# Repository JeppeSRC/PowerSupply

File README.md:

# PowerSupply
Software, schematic and layout for kind of a PSU

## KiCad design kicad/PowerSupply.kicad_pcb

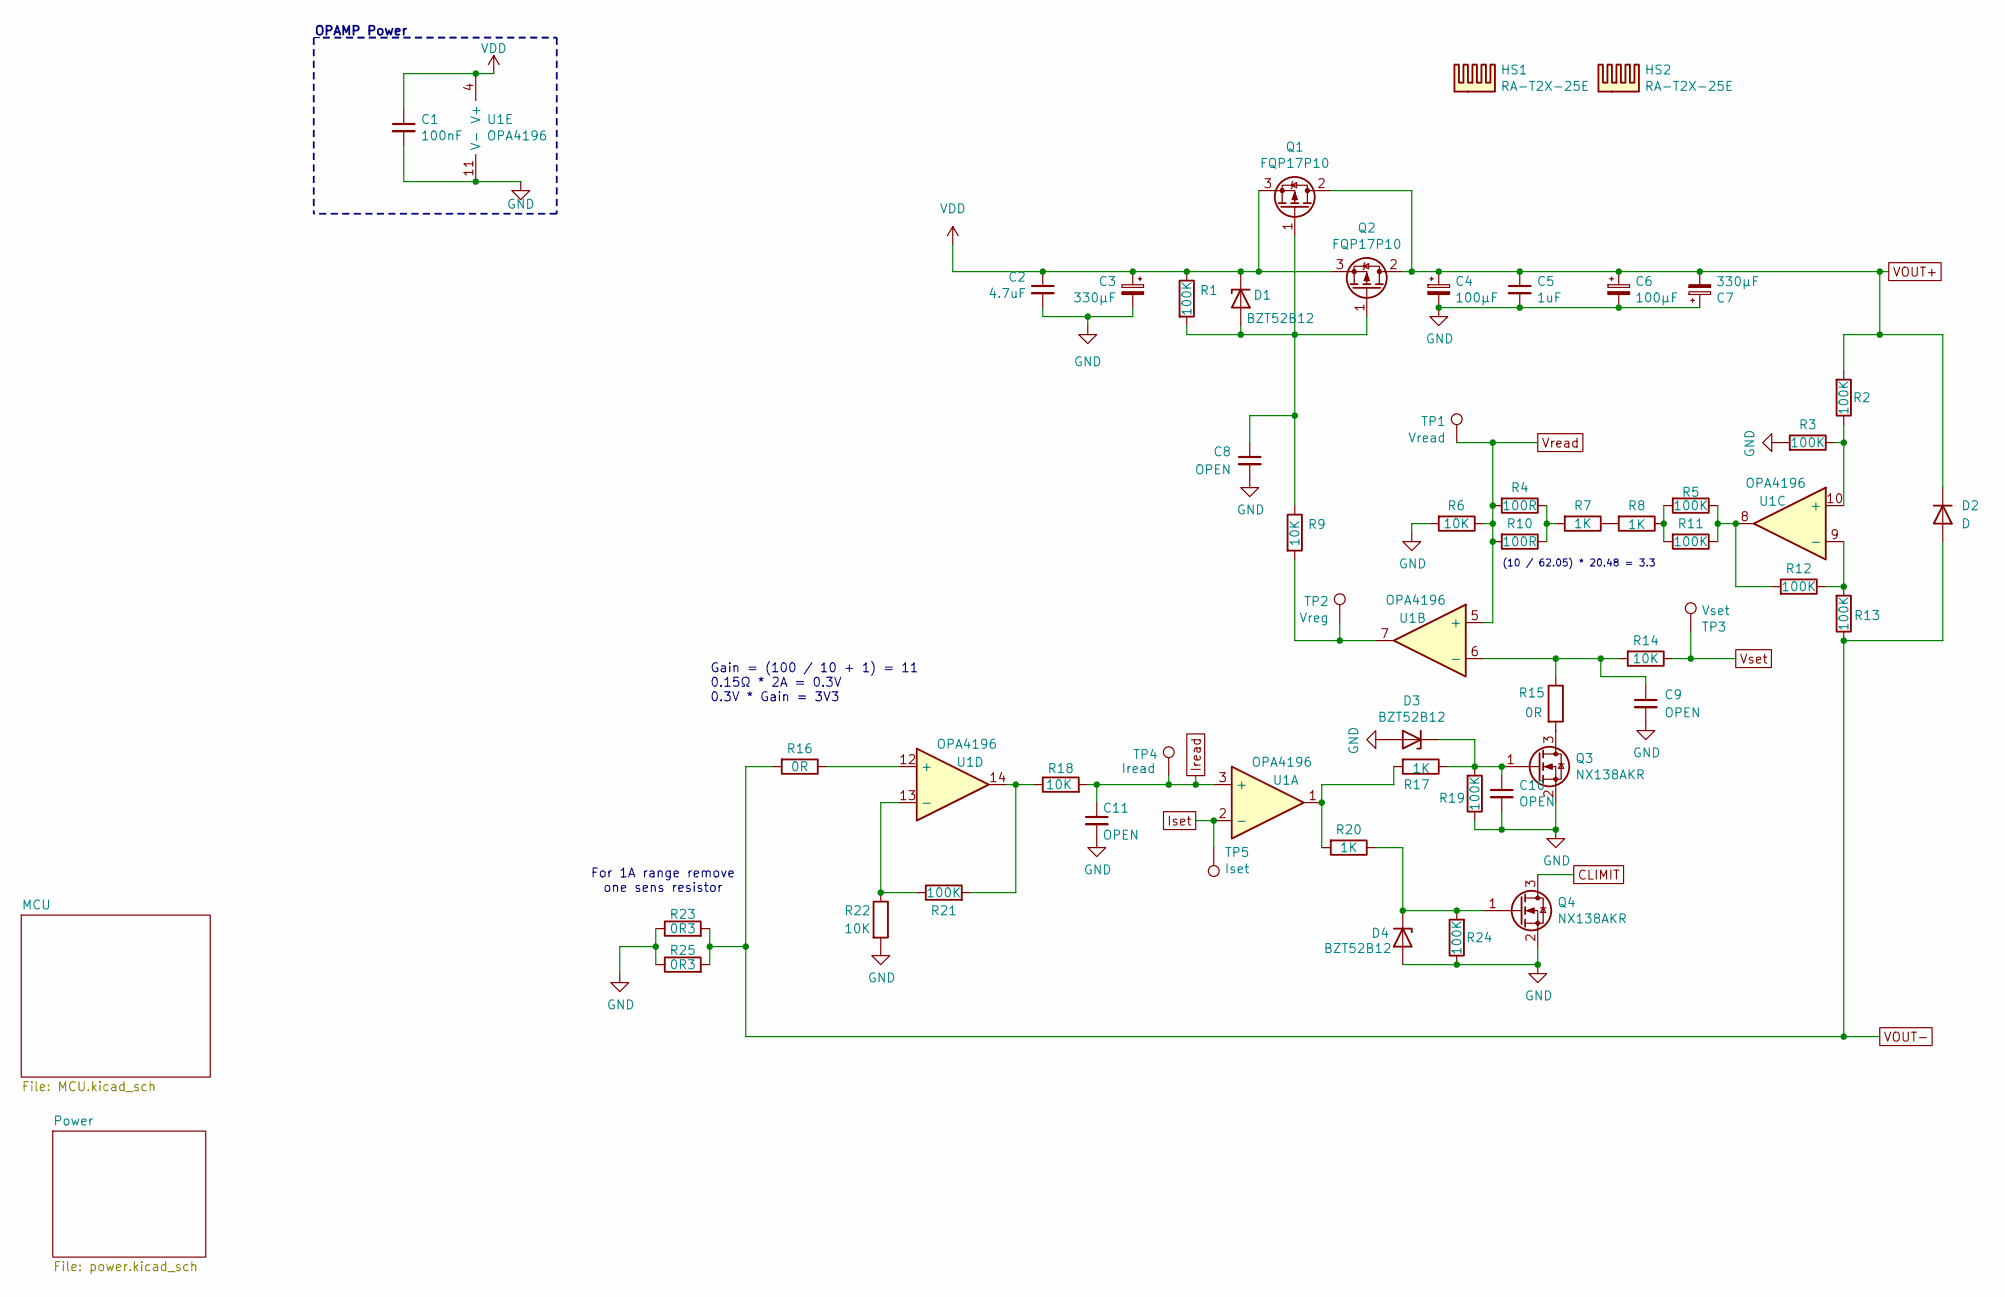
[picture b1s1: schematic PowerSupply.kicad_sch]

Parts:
C1: 100nF; C_0805_2012Metric_Pad1.18x1.45mm_HandSolder; MPN CC0805KRX7R9BB104
C2: 4.7uF; C_0805_2012Metric_Pad1.18x1.45mm_HandSolder; MPN GRM21BR61H475ME51L
C3, C7: 330µF; CP_Radial_D8.0mm_P3.50mm; MPN REA471M1EBK-1012P
C4, C6: 100µF; CP_Radial_D8.0mm_P3.50mm; MPN EKZN500ELL101MHB5D
C5: 1uF; C_0805_2012Metric_Pad1.18x1.45mm_HandSolder; MPN CL21B105KBFNNNF
C8, C9, C10, C11: OPEN; C_0805_2012Metric_Pad1.18x1.45mm_HandSolder
D1, D3, D4: BZT52B12; D_SOD-123; MPN BZT52B12
D2: D; D_SMA_Handsoldering
HS1, HS2: RA-T2X-25E; MPN RA-T2X-25E
Q1, Q2: FQP17P10; TO-220-3_Vertical; MPN FQP17P10
Q3, Q4: NX138AKR; SOT-23-3; MPN NX138AKR
R1, R2, R3, R5, R11, R12, R13, R19, R21, R24: 100K; R_0805_2012Metric_Pad1.20x1.40mm_HandSolder; MPN CRCW080510K0FKEAC
R4, R10: 100R; R_0805_2012Metric_Pad1.20x1.40mm_HandSolder; MPN RC0805FR-13100RL
R6, R9, R14, R18, R22: 10K; R_0805_2012Metric_Pad1.20x1.40mm_HandSolder; MPN RC0805FR-1310KL
R7, R8, R17, R20: 1K; R_0805_2012Metric_Pad1.20x1.40mm_HandSolder; MPN RC0805FR-131KL
R15, R16: 0R; R_0805_2012Metric_Pad1.20x1.40mm_HandSolder; MPN 0805W8J0000T5E
R23, R25: 0R3; R_0805_2012Metric_Pad1.20x1.40mm_HandSolder; MPN CRL1206-FW-R300ELF
TP1: Vread; TestPoint_Pad_D1.5mm
TP2: Vreg; TestPoint_Pad_D1.5mm
TP3: Vset; TestPoint_Pad_D1.5mm
TP4: Iread; TestPoint_Pad_D1.0mm
TP5: Iset; TestPoint_Pad_D1.0mm
U1: OPA4196; SOIC-14_3.9x8.7mm_P1.27mm; MPN OPA4196IDR

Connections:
CLIMIT: Q4.3 (D); also elsewhere on the board
GND: C1.2, C2.2, C3.2, C4.2, C5.2, C6.2, C7.1, C8.2, C9.2, C10.2, C11.2, D3.2 (A), D4.2 (A), Q3.2 (S), Q4.2 (S), R3.2, R6.2, R19.1, R22.2, R23.1, R24.1, R25.1, U1.11 (V-); also elsewhere on the board
Iread: C11.1, R18.2, TP4.1, U1.3 (+); also elsewhere on the board
Iset: TP5.1, U1.2 (-); also elsewhere on the board
unnamed: C8.1, D1.2 (A), Q1.1 (G), Q2.1 (G), R1.2, R9.1
unnamed: C10.1, D3.1 (K), Q3.1 (G), R17.1, R19.2
unnamed: D4.1 (K), Q4.1 (G), R20.1, R24.2
unnamed: Q3.3 (D), R15.2
unnamed: R7.1, R8.2
unnamed: R9.2, TP2.1, U1.7
unnamed: R4.1, R7.2, R10.1
unnamed: R5.1, R11.1, R12.2, U1.8
unnamed: R5.2, R8.1, R11.2
unnamed: R17.2, R20.2, U1.1
unnamed: R18.1, R21.2, U1.14
unnamed: C9.1, R14.2, R15.1, U1.6 (-)
unnamed: R2.1, R3.1, U1.10 (+)
unnamed: R12.1, R13.2, U1.9 (-)
unnamed: R16.1, U1.12 (+)
unnamed: R21.1, R22.1, U1.13 (-)
VDD: C1.1, C2.1, C3.1, D1.1 (K), Q1.3 (S), Q2.3 (S), R1.1, U1.4 (V+); also elsewhere on the board
VOUT+: C4.1, C5.1, C6.1, C7.2, D2.1 (K), Q1.2 (D), Q2.2 (D), R2.2; also elsewhere on the board
VOUT-: D2.2 (A), R13.1, R16.2, R23.2, R25.2; also elsewhere on the board
Vread: R4.2, R6.1, R10.2, TP1.1, U1.5 (+); also elsewhere on the board
Vset: R14.1, TP3.1; also elsewhere on the board

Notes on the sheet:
OPAMP Power
(10 / 62.05) * 20.48 = 3.3
Gain = (100 / 10 + 1) = 11 0.15Ω * 2A = 0.3V 0.3V * Gain = 3V3
For 1A range remove one sens resistor

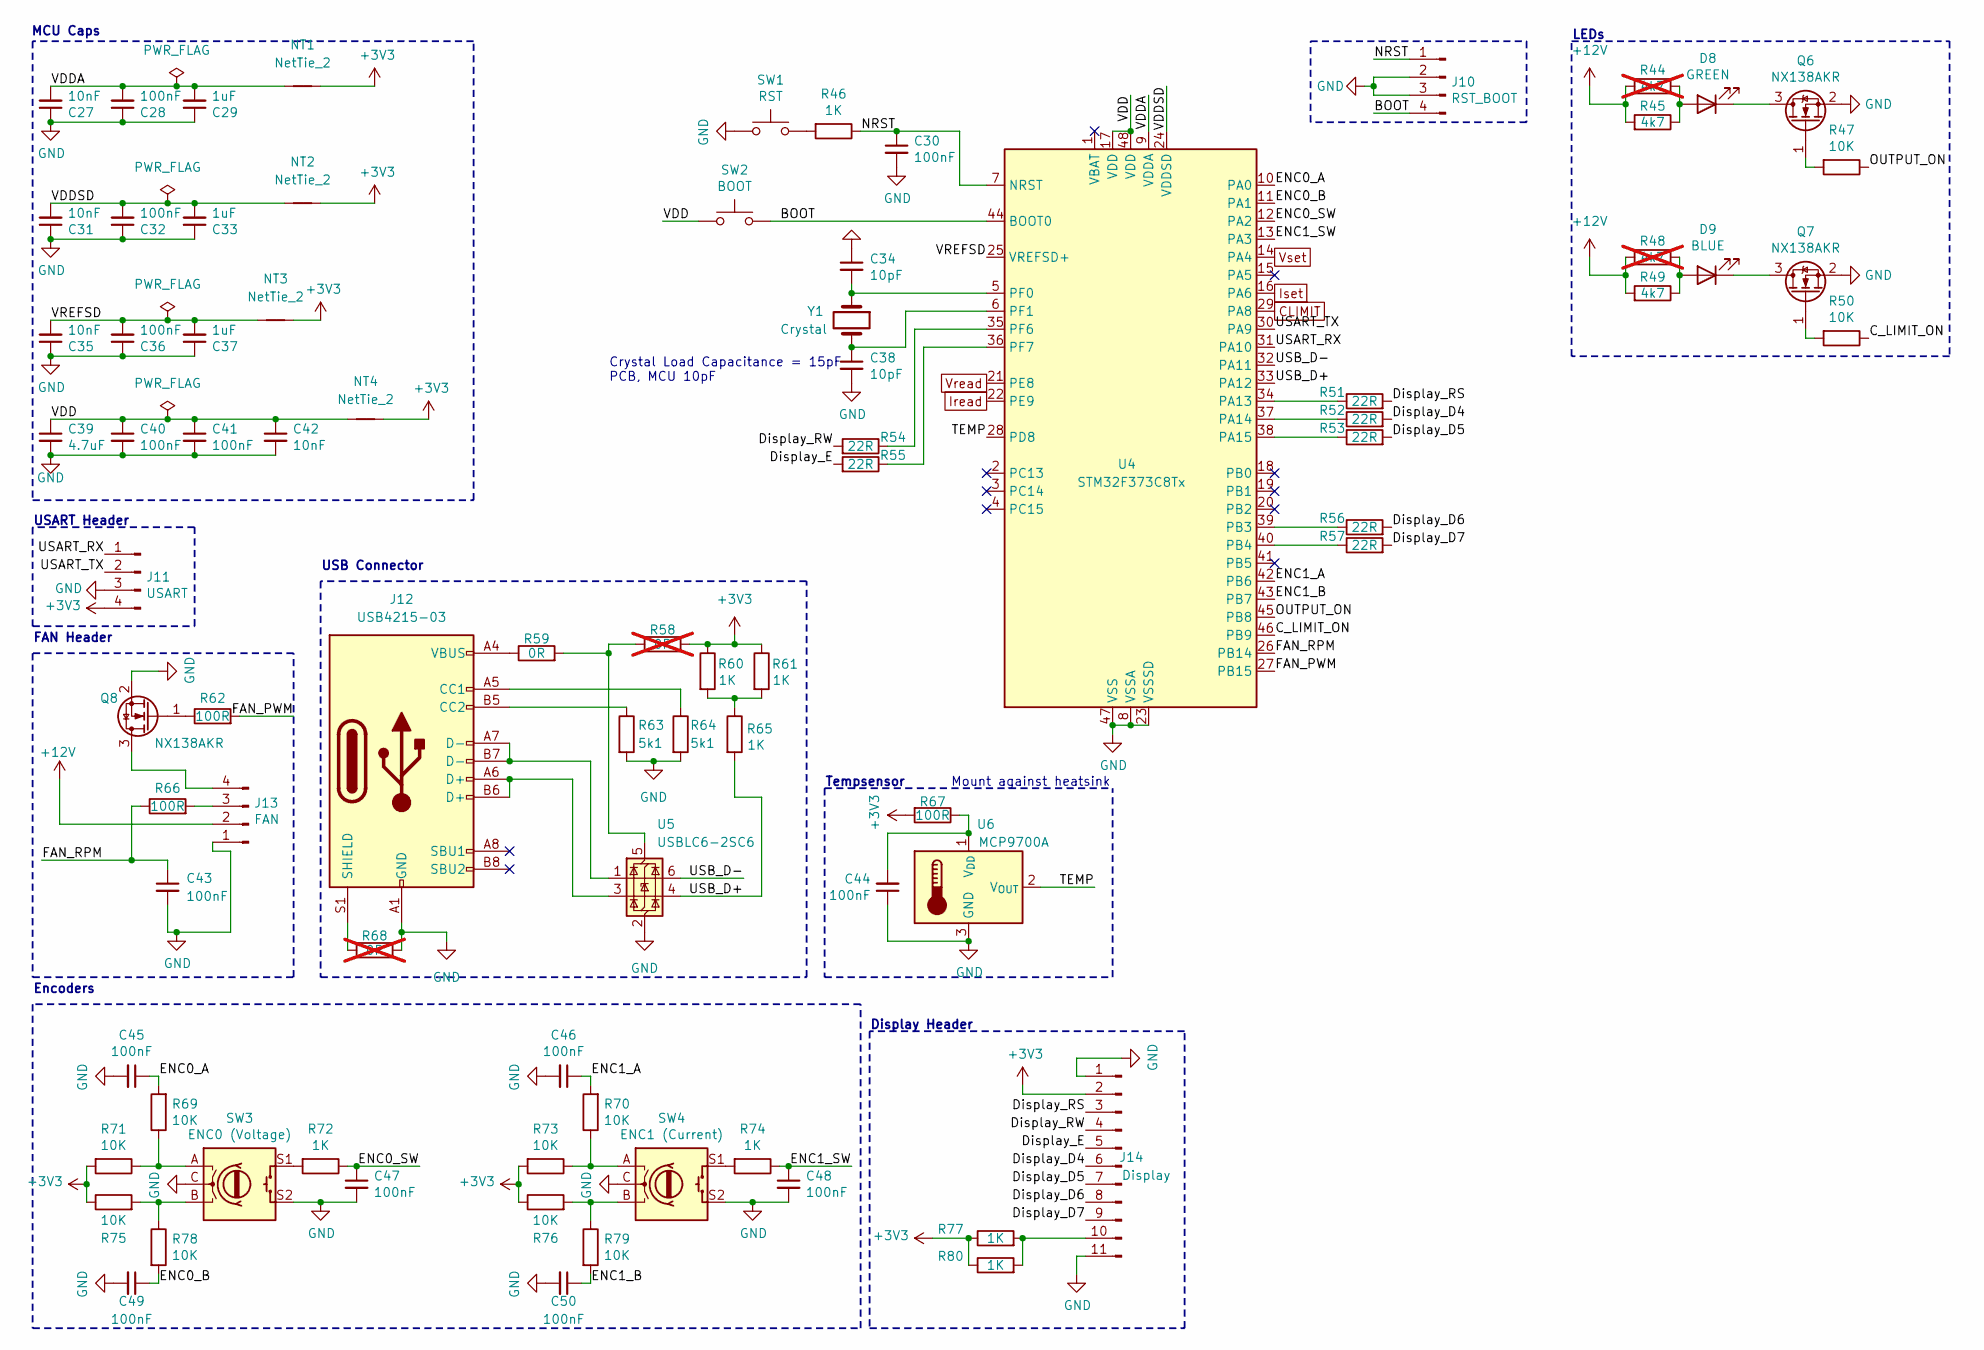
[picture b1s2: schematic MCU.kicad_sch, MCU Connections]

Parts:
C27, C31, C35, C42: 10nF; C_0805_2012Metric_Pad1.18x1.45mm_HandSolder; MPN CC0805KRX7R0BB103
C28, C30, C32, C36, C40, C41, C43, C44, C45, C46, C47, C48, C49, C50: 100nF; C_0805_2012Metric_Pad1.18x1.45mm_HandSolder; MPN CC0805KRX7R9BB104
C29, C33, C37: 1uF; C_0805_2012Metric_Pad1.18x1.45mm_HandSolder; MPN TMK212B7105KG-T
C34, C38: 10pF; C_0805_2012Metric_Pad1.18x1.45mm_HandSolder; MPN C0805C100J5GAC
C39: 4.7uF; C_0805_2012Metric_Pad1.18x1.45mm_HandSolder; MPN GRM21BR61H475ME51L
D8: GREEN; LED_1206_3216Metric_Pad1.42x1.75mm_HandSolder; MPN APTD3216LZGCK
D9: BLUE; LED_1206_3216Metric_Pad1.42x1.75mm_HandSolder; MPN APTD3216LVBCD
J10: RST_BOOT; PinHeader_1x04_P2.54mm_Vertical
J11: USART; PinHeader_1x04_P2.54mm_Vertical
J12: USB4215-03; USB_C_Receptacle_GCT_USB4215-xx; MPN USB4215-03
J13: FAN; FanPinHeader_1x04_P2.54mm_Vertical
J14: Display; PinHeader_1x11_P2.54mm_Vertical; MPN M20-9991646
NT1, NT2, NT3, NT4: NetTie_2; NetTie-2_SMD_Pad0.5mm
Q6, Q7, Q8: NX138AKR; SOT-23-3; MPN NX138AKR
R44, R48: 4k7; R_0805_2012Metric_Pad1.20x1.40mm_HandSolder; MPN CRCW080510K0FKEAC; not fitted
R45, R49: 4k7; R_0805_2012Metric_Pad1.20x1.40mm_HandSolder; MPN CRCW080510K0FKEAC
R46, R60, R61, R65, R72, R74, R77, R80: 1K; R_0805_2012Metric_Pad1.20x1.40mm_HandSolder; MPN RC0805FR-131KL
R47, R50, R69, R70, R71, R73, R75, R76, R78, R79: 10K; R_0805_2012Metric_Pad1.20x1.40mm_HandSolder; MPN RC0805FR-1310KL
R51, R52, R53, R54, R55, R56, R57: 22R; R_0805_2012Metric_Pad1.20x1.40mm_HandSolder; MPN RK73H2ATTDD22R0F
R58, R68: 0R; R_0805_2012Metric_Pad1.20x1.40mm_HandSolder; MPN 0805W8J0000T5E; not fitted
R59: 0R; R_0805_2012Metric_Pad1.20x1.40mm_HandSolder; MPN 0805W8J0000T5E
R62, R66, R67: 100R; R_0805_2012Metric_Pad1.20x1.40mm_HandSolder; MPN RC0805FR-13100RL
R63, R64: 5k1; R_0805_2012Metric_Pad1.20x1.40mm_HandSolder; MPN RK73H2ATTD5101F
SW1: RST; LL3301NF065QG; MPN TS04-66-55-BK-100-SMT
SW2: BOOT; LL3301NF065QG; MPN TS04-66-55-BK-100-SMT
SW3: ENC0 (Voltage); PEC12R-2xxxf-Sxxxx; MPN PEC12R-2220F-S0024
SW4: ENC1 (Current); PEC12R-2xxxf-Sxxxx; MPN PEC12R-2220F-S0024
U4: STM32F373C8Tx; LQFP-48_7x7mm_P0.5mm; MPN STM32F373C8Tx
U5: USBLC6-2SC6; SOT-23-6_Handsoldering
U6: MCP9700A; SOT-23; MPN MCP9700A
Y1: Crystal; Crystal_HC49-U_Vertical; MPN LFXTAL033206

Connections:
+3V3: J11.4, J14.2, NT1.2, NT2.2, NT3.2, NT4.2, R58.2, R60.1, R61.1, R67.2, R71.2, R73.2, R75.1, R76.1, R77.1, R80.1; also elsewhere on the board
+12V: J13.2, R44.2, R45.2, R48.2, R49.2; also elsewhere on the board
/MCU/BOOT: J10.4, SW2.1, U4.44 (BOOT0)
/MCU/C_LIMIT_ON: R50.1, U4.46 (PB9)
/MCU/Display_D4: J14.6, R52.2
/MCU/Display_D5: J14.7, R53.2
/MCU/Display_D6: J14.8, R56.2
/MCU/Display_D7: J14.9, R57.2
/MCU/Display_E: J14.5, R55.2
/MCU/Display_RS: J14.3, R51.2
/MCU/Display_RW: J14.4, R54.2
/MCU/ENC0_A: C45.1, R69.2, U4.10 (PA0)
/MCU/ENC0_B: C49.1, R78.2, U4.11 (PA1)
/MCU/ENC0_SW: C47.1, R72.1, U4.12 (PA2)
/MCU/ENC1_A: C46.1, R70.2, U4.42 (PB6)
/MCU/ENC1_B: C50.1, R79.2, U4.43 (PB7)
/MCU/ENC1_SW: C48.1, R74.1, U4.13 (PA3)
/MCU/FAN_PWM: R62.2, U4.27 (PB15)
/MCU/FAN_RPM: C43.1, R66.1, U4.26 (PB14)
/MCU/NRST: C30.1, J10.1, R46.1, U4.7 (NRST)
/MCU/OUTPUT_ON: R47.1, U4.45 (PB8)
/MCU/TEMP: U4.28 (PD8), U6.2 (V_{OUT})
/MCU/USART_RX: J11.1, U4.31 (PA10)
/MCU/USART_TX: J11.2, U4.30 (PA9)
/MCU/USB_D+: R65.2, U4.33 (PA12), U5.4 (I/O2)
/MCU/USB_D-: U4.32 (PA11), U5.6 (I/O1)
/MCU/VDD: C39.1, C40.1, C41.1, C42.1, NT4.1, SW2.2, U4.17 (VDD), U4.48 (VDD)
/MCU/VDDA: C27.2, C28.2, C29.2, NT1.1, U4.9 (VDDA)
/MCU/VDDSD: C31.2, C32.2, C33.2, NT2.1, U4.24 (VDDSD)
/MCU/VREFSD: C35.2, C36.2, C37.2, NT3.1, U4.25 (VREFSD+)
CLIMIT: U4.29 (PA8); also elsewhere on the board
GND: C27.1, C28.1, C29.1, C30.2, C31.1, C32.1, C33.1, C34.1, C35.1, C36.1, C37.1, C38.2, C39.2, C40.2, C41.2, C42.2, C43.2, C44.1, C45.2, C46.2, C47.2, C48.2, C49.2, C50.2, J10.2, J10.3, J11.3, J12.A1 (GND), J12.A12 (GND), J12.B1 (GND), J12.B12 (GND), J13.1, J14.1, J14.11, Q6.2 (S), Q7.2 (S), Q8.2 (S), R63.2, R64.2, R68.2, SW1.2, SW3.C, SW3.S2, SW4.C, SW4.S2, U4.8 (VSSA), U4.23 (VSSSD), U4.47 (VSS), U5.2 (GND), U6.3 (GND); also elsewhere on the board
Iread: U4.22 (PE9); also elsewhere on the board
Iset: U4.16 (PA6); also elsewhere on the board
unnamed: D8.2 (A), R44.1, R45.1
unnamed: D8.1 (K), Q6.3 (D)
unnamed: D9.2 (A), R48.1, R49.1
unnamed: D9.1 (K), Q7.3 (D)
unnamed: J12.A5 (CC1), R64.1
unnamed: J12.B5 (CC2), R63.1
unnamed: J12.A6 (D+), J12.B6 (D+), U5.3 (I/O2)
unnamed: J12.A7 (D-), J12.B7 (D-), U5.1 (I/O1)
unnamed: J12.S1 (SHIELD), R68.1
unnamed: J12.A4 (VBUS), J12.A9 (VBUS), J12.B4 (VBUS), J12.B9 (VBUS), R59.1
unnamed: J13.3, R66.2
unnamed: J13.4, Q8.3 (D)
unnamed: J14.10, R77.2, R80.2
unnamed: Q6.1 (G), R47.2
unnamed: Q7.1 (G), R50.2
unnamed: Q8.1 (G), R62.1
unnamed: R46.2, SW1.1
unnamed: R60.2, R61.2, R65.1
unnamed: R69.1, R71.1, SW3.A
unnamed: R70.1, R73.1, SW4.A
unnamed: R72.2, SW3.S1
unnamed: R74.2, SW4.S1
unnamed: R75.2, R78.1, SW3.B
unnamed: R76.2, R79.1, SW4.B
unnamed: R51.1, U4.34 (PA13)
unnamed: R52.1, U4.37 (PA14)
unnamed: R53.1, U4.38 (PA15)
unnamed: R56.1, U4.39 (PB3)
unnamed: R57.1, U4.40 (PB4)
unnamed: C34.2, U4.5 (PF0), Y1.1
unnamed: C38.1, U4.6 (PF1), Y1.2
unnamed: R54.1, U4.35 (PF6)
unnamed: R55.1, U4.36 (PF7)
unnamed: R58.1, R59.2, U5.5 (VBUS)
unnamed: C44.2, R67.1, U6.1 (V_{DD})
Vread: U4.21 (PE8); also elsewhere on the board
Vset: U4.14 (PA4); also elsewhere on the board

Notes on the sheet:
USART Header
LEDs
Mount against heatsink
FAN Header
Encoders
Display Header
Tempsensor
Crystal Load Capacitance = 15pF PCB, MCU 10pF
MCU Caps
USB Connector

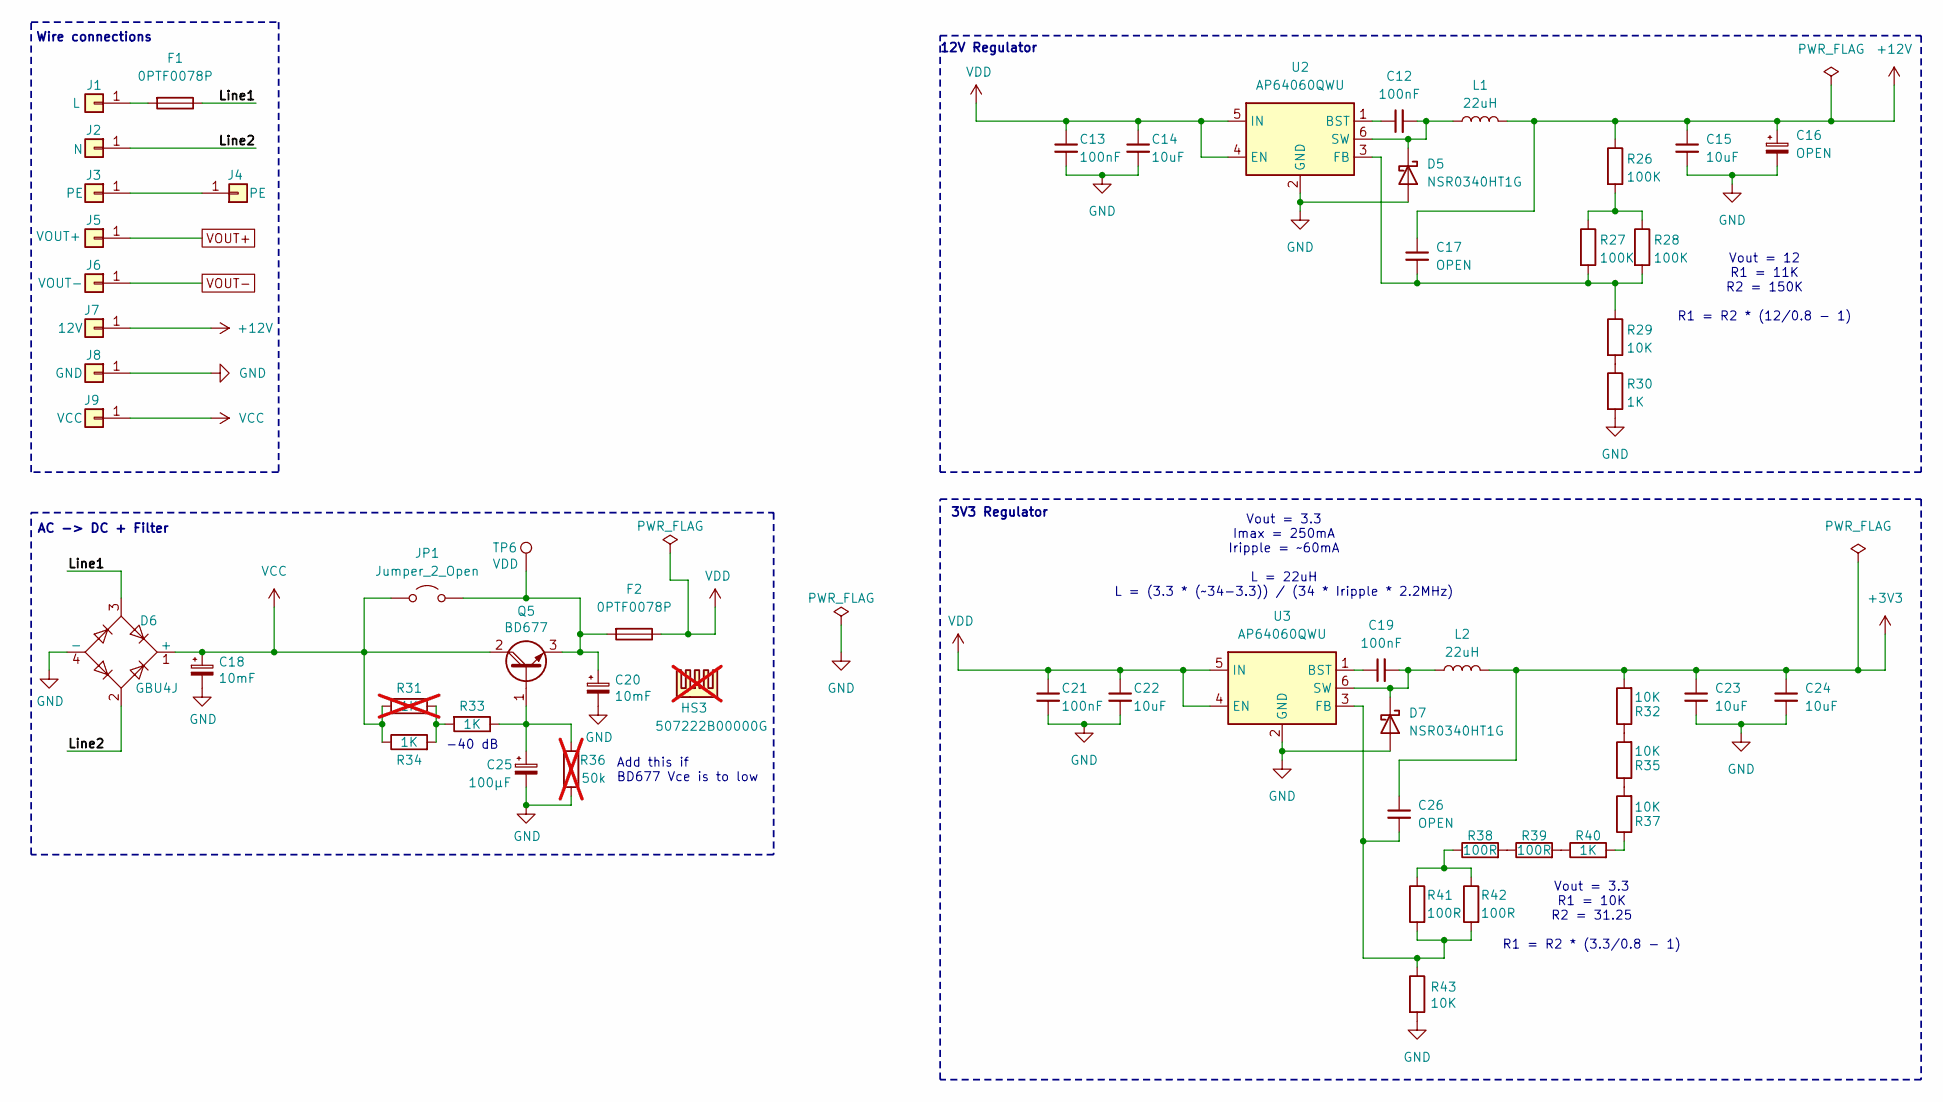
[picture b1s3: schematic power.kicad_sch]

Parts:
C12, C13, C19, C21: 100nF; C_0805_2012Metric_Pad1.18x1.45mm_HandSolder; MPN CC0805KRX7R9BB104
C14, C22: 10uF; C_1206_3216Metric_Pad1.33x1.80mm_HandSolder; MPN CL31A106KBHNNNE
C15, C23, C24: 10uF; C_0805_2012Metric_Pad1.18x1.45mm_HandSolder; MPN GRM21BR61E106KA73K
C16: OPEN; CP_Radial_D6.3mm_P2.50mm
C17, C26: OPEN; C_0805_2012Metric_Pad1.18x1.45mm_HandSolder
C18, C20: 10mF; CP_Radial_D30.0mm_P10.00mm_SnapIn
C25: 100µF; CP_Radial_D8.0mm_P3.50mm; MPN EKZN500ELL101MHB5D
D5, D7: NSR0340HT1G; D_SOD-323_HandSoldering; MPN NSR0340HT1G
D6: GBU4J; Diode_Bridge_Vishay_GBU; MPN GBU4J
F1, F2: 0PTF0078P; FuseHolder; MPN 0PTF0078P
HS3: 507222B00000G; not fitted
J1: L; TestPoint_Pad_4.0x4.0mm
J2: N; TestPoint_Pad_4.0x4.0mm
J3, J4: PE; TestPoint_Pad_4.0x4.0mm
J5: VOUT+; TestPoint_Pad_4.0x4.0mm
J6: VOUT-; TestPoint_Pad_4.0x4.0mm
J7: 12V; TestPoint_Pad_4.0x4.0mm
J8: GND; TestPoint_Pad_4.0x4.0mm
J9: VCC; TestPoint_Pad_4.0x4.0mm
JP1: Jumper_2_Open; SolderJumper-2_P1.3mm_Open_Pad1.0x1.5mm
L1, L2: 22uH; L_Coilcraft_MSS1246-XXX; MPN AMRM00101040220MA1
Q5: BD677; TO-126-3_Vertical; MPN BD677
R26, R27, R28: 100K; R_0805_2012Metric_Pad1.20x1.40mm_HandSolder; MPN CRCW080510K0FKEAC
R29, R32, R35, R37, R43: 10K; R_0805_2012Metric_Pad1.20x1.40mm_HandSolder; MPN RC0805FR-1310KL
R30, R33, R34, R40: 1K; R_0805_2012Metric_Pad1.20x1.40mm_HandSolder; MPN RC0805FR-131KL
R31: 1K; R_0805_2012Metric_Pad1.20x1.40mm_HandSolder; MPN RC0805FR-131KL; not fitted
R36: 50k; R_0805_2012Metric_Pad1.20x1.40mm_HandSolder; not fitted
R38, R39, R41, R42: 100R; R_0805_2012Metric_Pad1.20x1.40mm_HandSolder; MPN RC0805FR-13100RL
TP6: VDD; TestPoint_Pad_D1.5mm
U2, U3: AP64060QWU; TSOT-23-6; MPN AP64060QWU

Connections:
+3V3: C23.1, C24.1, C26.1, L2.2, R32.2; also elsewhere on the board
+12V: C15.1, C16.1, C17.1, J7.1, L1.2, R26.1; also elsewhere on the board
/Power/Line1: D6.3, F1.1
/Power/Line2: D6.2, J2.1
GND: C13.2, C14.2, C15.2, C16.2, C18.2, C20.2, C21.2, C22.2, C23.2, C24.2, C25.2, D5.2 (A), D6.4 (-), D7.2 (A), J8.1, R30.2, R36.1, R43.2, U2.2 (GND), U3.2 (GND); also elsewhere on the board
unnamed: C12.2, D5.1 (K), L1.1, U2.6 (SW)
unnamed: C19.2, D7.1 (K), L2.1, U3.6 (SW)
unnamed: F1.2, J1.1
unnamed: J3.1, J4.1
unnamed: C20.1, F2.2, JP1.2 (B), Q5.3 (E), TP6.1
unnamed: C25.1, Q5.1 (B), R33.1, R36.2
unnamed: R26.2, R27.1, R28.1
unnamed: R29.2, R30.1
unnamed: R31.1, R33.2, R34.2
unnamed: R32.1, R35.2
unnamed: R35.1, R37.2
unnamed: R37.1, R40.2
unnamed: R38.1, R41.1, R42.1
unnamed: R38.2, R39.1
unnamed: R39.2, R40.1
unnamed: C12.1, U2.1 (BST)
unnamed: C17.2, R27.2, R28.2, R29.1, U2.3 (FB)
unnamed: C19.1, U3.1 (BST)
unnamed: C26.2, R41.2, R42.2, R43.1, U3.3 (FB)
VCC: C18.1, D6.1 (+), J9.1, JP1.1 (A), Q5.2 (C), R31.2, R34.1
VDD: C13.1, C14.1, C21.1, C22.1, F2.1, U2.4 (EN), U2.5 (IN), U3.4 (EN), U3.5 (IN); also elsewhere on the board
VOUT+: J5.1; also elsewhere on the board
VOUT-: J6.1; also elsewhere on the board

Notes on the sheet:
12V Regulator
Wire connections
-40 dB
Vout = 3.3 Imax = 250mA Iripple = ~60mA L = 22uH L = (3.3 * (~34-3.3)) / (34 * Iripple * 2.2MHz)
Add this if BD677 Vce is to low
AC -> DC + Filter
Vout = 3.3 R1 = 10K R2 = 31.25 R1 = R2 * (3.3/0.8 - 1)
3V3 Regulator
Vout = 12 R1 = 11K R2 = 150K R1 = R2 * (12/0.8 - 1)

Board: 2 copper layers, 189 parts (0 on the bottom side), 112 nets, no tracks yet.

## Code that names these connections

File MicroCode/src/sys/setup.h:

#pragma once

/*	Device			Port			PhysicalPin
	ENC0_A			PA0				10
	ENC0_B			PA1				11
	ENC0_SW			PA2				12
	ENC1_A			PB6				42
	ENC1_B			PB7				43
	ENC1_SW			PA3				13
	----------------------------------
	Iset			PA5				15 DAC1_CH2
	Vset			PA6				16 DAC2_CH1
	----------------------------------
	Iread			PE9				22 SDADC2_AIN7P
	Vread			PE8				21 SDADC1_AIN8P
	----------------------------------
	CLIM			PA4				14
	.---------------------------------
	OUTPUT_ON		PB8				45
	C_LIMIT			PB9				46
	----------------------------------
	USART_TX		PA9				30
	USART_RX		PA10			31
	----------------------------------
	USB_D-			PA11			32
	USB_D+			PA12			33
	----------------------------------
	Display_RS		PA13			34
	Display_RW		PF6				35
	Display_E		PF7				36
	Display_D4		PA14			37
	Display_D5		PA15			38
	Display_D6		PB3				39
	Display_D7		PB4				40
 */


 // AHB		48 Mhz
 // APB2	48 Mhz
 // APB1	24 Mhz
 // SDADC	6  Mhz

 /* Display Format 2x16

	 ------------------
	 |S  00.00V 0.000A|
	 |O  00.00V 0.000A|
	 ------------------
 */

#define USE_HSE 1

#define NOP asm("mov r1, r1")

void Initialize();

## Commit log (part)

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2019-10-25 Rename
2019-10-26 Chagned MPN for some 10k resistors that doesn't need the precision
2019-10-26 Changed BOOT0 pullup to lower precision resistor
2019-10-26 Set R22 and R23 to 1k
2019-10-26 Fixed MPN and datasheet
2019-10-26 Changed value on D1 and D2 to the color they emit
2019-10-27 Added VID and PID
2019-10-29 Fixed linker script
2019-10-29 Fixed startup
2019-10-30 Rewrite ahb1
2019-10-30 Fixed setup.c
2019-10-30 Minor change
2019-10-30 Added volatile
2019-10-30 Fixed time.c
2019-11-05 Using TIM7 for DelayMillis
2019-11-05 Fixed strlen
2019-11-05 Display initialization now works!
2019-11-05 Added NOP and enabled HSE
2019-11-05 Removed old code and converted to use the BSRR register on the first E toggle
2019-11-05 Changed to BSRR register in error
2019-11-05 Calling Delay functions once to unfuck them once and for all
2019-11-05 Prints Hello word in main
2019-11-09 Added functions to enable and disable interrupts
2019-11-09 Stuff
2019-11-16 Bunch of things
2019-12-05 Removed everything in main to start over
2019-12-05 Timer macros
2019-12-05 Restored string.c
2019-12-05 Added simple test code to test sprintf
2019-12-07 Enable clocks for TIM19 and TIM4
2019-12-07 Line#
2019-12-07 Maybe fixed sprintf
2019-12-07 Fixed sprintf for real
2019-12-07 Included stdarg.h instead of using own implementation
2019-12-07 added const
2019-12-07 Simplified append
2019-12-08 Fix memcpy
2019-12-08 Replaced append function with APPEND macro
2019-12-08 Updated to a cooler example
2019-12-08 Added DisplayPrintChar
2019-12-08 Added vsprintf
2019-12-08 Implemented DisplayPrintf and other small fixes
2019-12-08 Configured IO ports for the encoders
2019-12-15 Removed stdarg
2019-12-15 Renamed files and small fixes
2019-12-15 Changed to g++
2019-12-15 Removed unsused stuff
2019-12-15 Slight optimization
2019-12-15 Converted display to a class
2019-12-15 Replaced old display calls
2019-12-15 Potential USART implementation
2019-12-15 Added files
2019-12-16 Minor changes
2020-03-28 Added FLASH_ACR register
2020-03-28 Added flas wait state and new sdadc code
2020-03-28 HSE on by default
2020-03-28 Removed commented code
2020-03-28 Fixed thing
2020-03-29 Removed LTO
2020-03-29 Added Enable and DisableInterrupts function
2020-03-29 Disable interrupts before issuing commands to the display
2020-03-29 Minor changes"
2020-03-29 Setting voltage to dac and printing to screen
2020-03-29 Removed unused cODE
2020-04-03 TMP commit
2020-04-03 some kind of encoder implementation
2020-04-03 Enabling interrupts
2020-04-03 Added MC_VERSION define
2020-04-03 Added pragma once to all files
2020-04-03 some ui stuff
2020-04-03 Added FPU registers
2020-04-03 enable FPU code
2020-04-03 Added compiler arguments
2020-04-03 Added conveniece function
2020-04-03 Minor fix
2020-04-03 Updated main
2020-04-03 Removed old debug shit
2020-04-03 Printing Default_Handler to display when entered
2020-04-03 Fixed Millies and Micros
2020-04-03 Working encoders with velocity control
2020-04-04 Subtract 1 from delay in delay functions
2020-04-04 Added datasheets
2020-04-04 Project structure changes
2020-04-04 Added TODO list
2020-04-04 Fixed leds
2020-04-04 Connected Iread and Vread to ADC as well
2020-04-04 Added additional btn for boot0 selection during reset
2020-04-04 balls
2020-04-04 Input and Output capacitance
2020-04-04 Correction
2020-04-05 Changed input and output capacitance
2020-04-05 Changed led fets to the correct symbol
2020-04-05 Added todo
2020-04-12 Doc changes
2020-04-12 Removed RC filter on VReg ouypuy
2020-04-12 Changed current limiting circuit
2020-04-12 Moved U2B to adc input
2020-04-12 LMAO
2020-04-12 Added LM317 symbol
2020-04-12 12V regulator
2020-04-12 Added net ties to MCU power pins
2020-04-12 Added LM317 datasheet
2020-04-13 Changed velocity factor to 200
2020-04-13 Changed iSet and vSet to floats
2020-04-13 Removed a bunch of empty lines
2020-04-13 Changed iSet min to 10
2020-04-13 Changed gate resistor values
2020-04-13 Added PowerSupply title
2020-04-13 Added PWM fan specification
2020-04-13 removed stuff
2020-04-13 Restructured schematic to be on one A3 page
2020-04-13 Added fan header
2020-04-13 Added 1µF output cap to 12V rail and changed 100nF cap on LM317 ADJ pin to 1µF
2020-04-13 Changed cap type
2020-04-13 -Removed 1k resistor on VReg output -Added cap and extra resistor spot
2020-04-13 changed some stuff
2020-04-23 Updated spec
2020-04-23 Changed current shunt
2020-04-23 Added MPN and footprint to shunt resistor
2020-04-23 Added shunt datasheet
2020-04-24 Changed current sense stuff again
2020-04-24 Added zener to moset
2020-04-24 Added schottky diode across LD1086 regulator
2020-04-24 Changed resistor mpn
2020-04-24 Slight schematic restructure
2020-04-26 Added 3D model to heatsink
2020-04-26 Changed color of pin in step file
2020-04-26 Added 3D model for encoders
2020-04-26 Added USB 3D model
2020-04-26 Buttload of changes
2020-04-26 EEEEH
2020-04-26 Things
2020-04-27 Fixed LM317 Symbol
2020-04-27 Fixed docs
2020-04-27 Added 100K pulldowns to fet gates
2020-04-27 Added temperature sensor
2020-04-27 Added something idk what to call
2020-04-27 Forgot a resistor lel
2020-04-27 Udated readme
2020-04-27 Added flyback diode to fan connector
2020-04-27 Removed unused stuff¨
2020-04-27 Removed unnecessary stuff
2020-05-01 Added USB registers
2020-05-01 Noewq
2020-05-01 Fixed usb defines and included usb.h in registers.h
2020-05-01 Fixed BTABLE
2020-05-10 Endpoint 1
2020-05-10 Initial USB com spec thingy
2020-05-11 Changed VID:PID and another minor change
2020-05-11 Only setup endpoint 1 when deviceState is Addressed
2020-05-11 IDFK
2020-05-18 Changed definition of FanRPM and added FanSpeed
2020-05-19 Fixed shunt resistor value
2020-05-19 Disconnected USB shield from ground
2020-05-20 Fixed incorrect pin mode
2020-05-20 100nF cap on reset pin
2020-05-20 Set speed on all GPIO ports to slow
2020-05-20 Added USB ESD suppressionand 1.5k pullup is derived from 5V VBUS
2020-05-20 Added noise suppression on MCP9700A
2020-05-20 Changed filter caps on encoders to 100nF
2020-05-20 Fixed weirdness
2020-05-20 Added binary printing to sprintf
2020-05-22 Fixed USART
2020-05-22 More USART functions
2020-05-23 Some usb stuff
2020-05-23 Fixed GPIO options for USB
2020-05-23 OOPSIE
2020-05-23 Moved PWR registers to its own file
2020-05-23 Moved DAC registers
2020-05-23 Moved Timers
2020-05-23 More timers
2020-05-23 Moved sdadc
2020-05-23 Moved flash
2020-05-23 Moved usart
2020-05-23 Moved rcc
2020-05-23 Moved syscfg
2020-05-23 Moved gpio
2020-05-23 Deleete
2020-05-23 Addeed all files to registers.h
2020-05-23 Added dma registers
2020-05-23 Stupid filteres not saving
2020-05-23 Added dma stuff
2020-05-23 Multiy byte USART transfers now use DMA for asynchronous transfers
2020-05-23 Semi worliong USB#
2020-05-26 Changes for kicad 5.1.6
2020-05-26 Removed OPA4196 from symbols
2020-07-03 Things that make no diffeerence
2020-07-03 Fixed incorrect field size
2020-07-08 Fixed labels
2020-07-08 Fixed LD1086 symbol cus it was fuckede
2020-07-08 Fixed LM317 symbol cus it was fuckede
2020-07-08 Fixed field name
2020-07-08 Minor schematic fixes
2020-09-14 Docs on things
2020-09-14 Added things that makes it possible to have 2 current ranges
2020-09-14 Updated spec to be more accurate
2020-09-16 More complete range selection
2020-09-16 Fixed wonkyness
2020-09-26 Part list for stuff that wont be in the schematic BOM
2020-09-26 Board files from Fusion
2020-09-27 Added MPNs
2020-09-30 Added AP64352 datasheet and symbol
2020-09-30 Added 12 buck converter
2020-09-30 Test points
2020-09-30 Changed input connection
2020-10-07 Added thingy
2020-10-09 IDK to much to remember
2020-10-09 Conneceted missing net
2020-10-10 Pre regulator
2020-10-10 Removed 3 pass transistors
2020-10-10 LEDs get power from 12V rail
2020-10-10 Fixed net-ties
2020-11-01 Updated init script to download latest version of FuckMake
2021-02-03 Fixed another typo
2021-02-04 Changed pre regulator
2021-02-04 Added another hs and pass transistor
2021-02-04 Updated changes.txt
2021-02-05 Changed pre regulator 21.6V from 20,96
2021-02-05 Swapped some symbols to builtin ones
2021-02-06 I think the filter is done
2021-02-06 Made it neater
2021-02-06 Changed stuff with leds
2021-02-06 Updated text
2021-02-06 Clear all annotations
2021-02-07 Added 5V regulator
2021-10-23 Fixed usb sram copy functions
2021-10-26 Removed unnecessary compiler flag
2021-10-26 Added USB LANGID spec
2021-10-26 Moved iSet, vSet, iRead, vRead to PSU class
2021-10-26 Working USB enumeration
2021-10-26 Preliminary USB interface spec
2021-10-26 Added calibration data to usb spec
2021-10-26 Added IN packet preload to usb spec
2021-10-26 Updated usage of ICALI and VCALI in Attributes
2021-10-26 Added CICALI and CVCALI to clear user calibration
2021-10-26 Clarification in spec
2021-10-26 Changed display layout
2021-10-26 Moved CLAMP macro from main to def.h
2021-10-26 Moved SetV and SetI stuff to PSU class
2021-10-26 Fixed bug where the display doesn't function on power up
2021-10-26 Moved UI::Initializee
2021-10-26 Preliminary implementation of usb communication
2021-10-27 Removed unused function declaration
2021-10-27 Changed SDADC clock speed
2021-10-27 Revert "Changed SDADC clock speed"
    This reverts commit 8c4e95876994d37a59634fb656bc83a2be234fdb.
2021-10-27 Yeeted unnecessary file
2021-10-27 Fixed SDADC initialization
2021-10-27 Fixed potential future bug
2021-10-27 Boot logging on USART
2021-10-27 Changed USART DMA priority
2021-10-27 SDADC conversions with DMA transfers
2021-10-27 Minor optimization
2021-10-28 Changed printf to print
2021-10-28 Moved FPU initialization to boot code
2021-10-28 TMP voltage read
2021-10-29 Fix while using old PCB
2021-11-01 More betterer, less copying
2021-11-01 Formatting
2021-11-01 Moved encoder interrupts to encoder.cpp
2021-11-01 SDADC no longer use DMA, convertions started manually
2021-11-01 Added comment
2021-11-01 Fixed rename error
2021-11-01 Initalize Data1 and Data2 structs
2021-11-04 Fixed current range going below 0 and looping around
2022-02-27 Upgraded kicad files to Kicad 6
2022-03-12 Fixed broken connections
2022-09-23 Moved buffer
2022-09-23 Meeh
2022-09-23 Fixed tabs
2022-09-23 Added rebuild targete
2022-09-23 Added -flto
2022-09-23 Addeed latest version of fuckmake to the init script
2022-09-28 Yeeted SMPSs and small changes
2022-09-28 Yeeted old PCB layout
2022-09-28 Updated encoder footprint
2022-09-29 Added option to power the 1K5 pullup from 3V3 or VBUS
2022-10-02 Fixed fan rpm reading circuitry
2022-10-02 Added LM317 for 12V regulation
2024-08-18 Updated files to kicad 8
2024-08-19 Fixed a bunch of alignment
2024-08-19 Added -ffreestanding to CFLAGS
2025-08-12 Updated to Kicad 9
2025-08-12 Blyat
2025-08-12 Stupid line endings
2025-08-12 Renamed datasheet
2025-08-12 Added datasheet
2025-08-12 Small changes and fixes after updating to Kicad 9
2025-08-12 Renamed VDD1 to VDD
2025-08-12 Copied outline to EdgeCuts layer
2025-08-13 Moved 3D model to fit the footprint
2025-08-13 PCB stuff
2025-08-13 Removed unnecessary stuff on fan tacho output
2025-08-13 Schematic work
2025-08-14 Formulas for rectifier
2025-08-14 Bunch of stuff
2025-08-14 vs code workspace
2025-08-14 Removed TLV197. Replaced AS324 with OPA4196
    Removed buffer on Vread
    Replaced AS324 with OPA4196
    Use the free channel (previously used as a buffer on Vrea)d instead of
    TLV197 for current sense applification
2025-08-14 Added VOUT- label
2025-08-14 Added fuse holder and replaced bridge rectifier UD4KB100 with GBU4J
2025-08-14 Added PE connections and pads for VOUT+ VOUT-
2025-08-15 Added series termination on display lines
2025-08-15 Added AP64060QWU symbol
2025-08-15 Changes and added Buck converter for 3V3
2025-08-16 Added cap on Vreg
2025-08-18 Removed some unused datasheets
2025-08-18 Added more caps on SMPS outputs
    - Added pin header for BOOT and RST
    - Re added USBLC6-2SC6
    - can be connected to VBUS or 3V3
    - 0R option to connect usb shield to GND
    - Added solder pad for 12V
2025-08-21 Removed unnecessary caps and other shit
2025-09-10 Moved FAN_RPM to pin PB14
2025-09-10 Fixed periipheral table
    ENC1 was had PA6 and PA7 in pins but should be PB6 and PB7
2025-09-13 DXF files for board and mounting holes
2025-09-13 Fixed bug in schematic
